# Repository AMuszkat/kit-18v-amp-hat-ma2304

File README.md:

# kit-18v-amp-hat-ma2304

A Raspberry Pi sound card with two MA2304xNS Class-D amplifiers and an MP3428 boost converter that powers the amps from a single- or dual-cell battery. For portable and mains powered applications.

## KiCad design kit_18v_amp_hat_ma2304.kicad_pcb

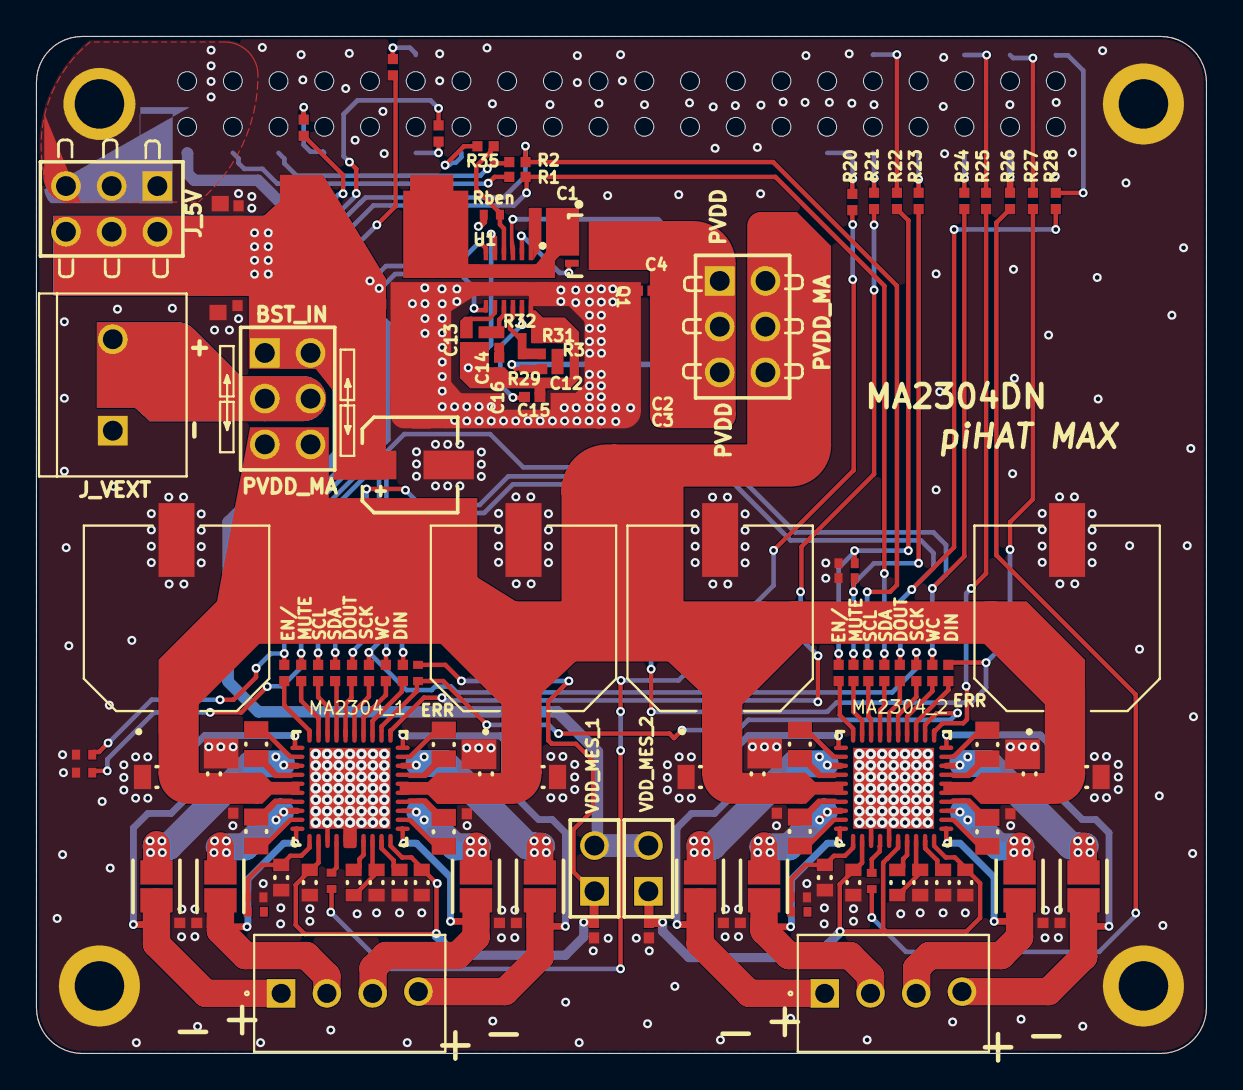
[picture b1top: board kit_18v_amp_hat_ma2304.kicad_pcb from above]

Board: 4 copper layers, 65.0 x 56.5 mm, 137 parts (1 on the bottom side), 107 nets.

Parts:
C1, C4, C10, C11, C13, C15, C16, C18, C19_1, C19_2: Cap; CAP0402_IPC_B
C2, C3, C6, C7: Cap; CAP1206_IPC_B
C5: EMZR350ARA470ME61G; PNSC-FT-V-53x53-2_V
C8, C9, C17: Cap; CAP0603_IPC_B
C12, C14: NP 0402; CAP0402_IPC_B
CADC_IN_1, CADC_IN_2: NP 0603; CAPC0603(1608)100_L
Cavdd_reg_1, Cavdd_reg_2: Cap; CAPC0603(1608)100_L
Ccd_dig_1, Ccd_dig_2: Cap; CAPC0603(1608)100_L
CflyA0_1, CflyA0_2, CflyA1_1, CflyA1_2: Cap; CAPC0805(2012)145_L
CflyB0_1, CflyB0_2, CflyB1_1, CflyB1_2: Cap; CAPC0805(2012)145_L
Cout0A_1, Cout0A_2, Cout0B_1, Cout0B_2, Cout1A_1, Cout1A_2, Cout1B_1, Cout1B_2: Cap; CAP0402_IPC_B
Cpvdd00_1, Cpvdd00_2, Cpvdd01_1, Cpvdd01_2, Cpvdd10_1, Cpvdd10_2, Cpvdd11_1, Cpvdd11_2: Cap; CAP0402_IPC_B
Cpvdd02_1, Cpvdd02_2, Cpvdd12_1, Cpvdd12_2: Cap; CAPC0603(1608)100_L
Cpvdd03_1, Cpvdd03_2, Cpvdd13_1, Cpvdd13_2: Cap; CAPC0805(2012)145_L
Cpvdd04_1, Cpvdd14_1: CAP; CAP_EEEFN1E821UL
Cpvdd04_2, Cpvdd14_2: Cap; CAP_EEEFN1E821UL
Cvdd_1, Cvdd_2: Cap; CAPC0603(1608)100_L
Cvdd_IO_1, Cvdd_IO_2: Cap; CAPC0603(1608)100_L
Cvdd_reg_1, Cvdd_reg_2: Cap; CAPC0603(1608)100_L
J_5V: 61300621121
J_PVDD: 61300621121
J_VEXT: 282837-2; TE_282837-2
J_VSEL: 61300621121
Jout1, Jout2: 282834-4; HDRV4W85P254_4X1_1062X650X1000
L1: Inductor; MPX1D0840
Lout0A_1, Lout0A_2, Lout0B_1, Lout0B_2, Lout1A_1, Lout1A_2, Lout1B_1, Lout1B_2: Ferrite; FP-NFZ2MSD-IPC_B
MA2304_1, MA2304_2: MA120_A23; QFN50P600X600X100_HS-41N
P1: Header 20X2; CLH-120-F-D-BE
Q1: IRFHM830PbF; FP-PQFN3_3x3_3-B-MFG
R1, R2, R4, R5, R6, R7, R8, R9, R10, R11, R12, R13, R14, R15, R16, R17, R18, R19, R20, R21, R22, R23, R24, R25, R26, R27, R28, R30, R33, R34, R35: 18r 0402 1%; RES0402_IPC_B
R3: NP 0402; RESC0402(1005)_L
R29, R31: Res; RESC0402(1005)_L
R32: Cap; RESC0402(1005)_L
RADC_IN1_1, RADC_IN1_2, RADC_IN2_1, RADC_IN2_2: Res; RESC0402(1005)_L
RMSEL_1, RMSEL_2: Res; RESC0402(1005)_L
Rben: Res; RESC0402(1005)_L
Ren1, Ren2: Res; RESC0402(1005)_L
Rmute1, Rmute2: Res; RESC0402(1005)_L
Rpwm_sync: Res; RESC0402(1005)_L
U1: MP3428AGL
VDD_MES_1, VDD_MES_2: 61300211121

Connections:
AMP1_ENABLE: R9.1, R16.1, Ren1.2
AMP1_ERR: MA2304_1.11, R21.1
AMP1_MSEL: R20.1, RMSEL_1.1
AMP1_MUTE: R14.1, R34.1, Rmute1.2
AMP2_ENABLE: R17.1, R22.2, Ren2.2
AMP2_ERR: MA2304_2.11, R25.2
AMP2_MSEL: R26.1, RMSEL_2.1
AMP2_MUTE: R15.1, R23.1, Rmute2.2
BST_EN: R35.1, Rben.2, U1.4
BST_IN: C5.1, C6.2, C7.2, C8.2, C9.2, C10.2, C11.2, C17.2, C18.2, J_5V.2, J_5V.4, J_5V.6, J_VSEL.1, J_VSEL.2, L1.1, U1.6, U1.11
ENABLE_1: MA2304_1.20, R16.2
ENABLE_2: MA2304_2.20, R17.2
GND: C2.1, C3.1, C4.1, C5.2, C6.1, C7.1, C8.1, C9.1, C10.1, C11.1, C17.1, C18.1, C19_1.1, C19_2.1, CADC_IN_1.2, CADC_IN_2.2, Cavdd_reg_1.2, Cavdd_reg_2.2, Cout0A_1.2, Cout0A_2.2, Cout0B_1.1, Cout0B_2.1, Cout1A_1.2, Cout1A_2.2, Cout1B_1.1, Cout1B_2.1, Cpvdd00_1.1, Cpvdd00_2.1, Cpvdd01_1.1, Cpvdd01_2.1, Cpvdd02_1.1, Cpvdd02_2.1, Cpvdd03_1.2, Cpvdd03_2.2, Cpvdd04_1.2, Cpvdd04_2.2, Cpvdd10_1.1, Cpvdd10_2.1, Cpvdd11_1.1, Cpvdd11_2.1, Cpvdd12_1.1, Cpvdd12_2.1, Cpvdd13_1.2, Cpvdd13_2.2, Cpvdd14_1.2, Cpvdd14_2.2, Cvdd_1.2, Cvdd_2.2, Cvdd_IO_1.2, Cvdd_IO_2.2, Cvdd_reg_1.2, Cvdd_reg_2.2, J_VEXT.1, MA2304_1.33, MA2304_1.35, MA2304_1.36, MA2304_1.41, MA2304_2.33, MA2304_2.35, MA2304_2.41, P1.6, P1.9, P1.14, P1.20, P1.25, P1.30, P1.34, P1.39, RADC_IN1_1.1, RADC_IN1_2.1, Rben.1, Ren1.1, Ren2.1, Rmute1.1, Rmute2.1, U1.9, U1.10, U1.17, U1.18, U1.22
I2C_SCL: R2.1, R30.1, R33.1
I2C_SCL_1: MA2304_1.18, R30.2
I2C_SCL_2: MA2304_2.18, R33.2
I2C_SDA: R1.1, R18.1, R19.1
I2C_SDA_1: MA2304_1.17, R18.2
I2C_SDA_2: MA2304_2.17, R19.2
I2S/TDM_DI_1: MA2304_1.16, R12.2
I2S/TDM_DI_2: MA2304_2.16, R13.2
I2S/TDM_DO_1: MA2304_1.13, R4.2
I2S/TDM_DO_2: MA2304_2.13, R5.2
I2S/TDM_SCK_1: MA2304_1.15, R10.2
I2S/TDM_SCK_2: MA2304_2.15, R11.2
I2S/TDM_WC_1: MA2304_1.14, R6.2
I2S/TDM_WC_2: MA2304_2.14, R8.2
I2S_DIN: R4.1, R5.1, R27.2
I2S_DOUT: R12.1, R13.1, R28.2
I2S_SCK: R7.2, R10.1, R11.1
I2S_WC: R6.1, R8.1, R24.1
MP_AGND: C13.2, C14.1, C15.1, C16.1, R31.2, U1.5, U1.16
MUTE_1: MA2304_1.19, R14.2
MUTE_2: MA2304_2.19, R15.2
NetC1_1: C1.1, L1.2, Q1.1, Q1.2, Q1.3, U1.7, U1.8, U1.19, U1.20, U1.21
NetC1_2: C1.2, U1.1
NetC12_1: C12.1, R3.1
NetC13_1: C13.1, U1.12
NetC14_2: C14.2, R32.1, U1.13
NetC15_2: C15.2, U1.15
NetC16_2: C16.2, R32.2
NetCADC_IN_1_1: CADC_IN_1.1, MA2304_1.31, RADC_IN1_1.2, RADC_IN2_1.2
NetCADC_IN_2_1: CADC_IN_2.1, MA2304_2.31, RADC_IN1_2.2, RADC_IN2_2.2
NetCavdd_reg_1_1: Cavdd_reg_1.1, MA2304_1.39
NetCavdd_reg_2_1: Cavdd_reg_2.1, MA2304_2.39
NetCcd_dig_1_1: Ccd_dig_1.1, Cvdd_reg_1.1, MA2304_1.38
NetCcd_dig_1_2: Ccd_dig_1.2, MA2304_1.37
NetCcd_dig_2_1: Ccd_dig_2.1, Cvdd_reg_2.1, MA2304_2.38
NetCcd_dig_2_2: Ccd_dig_2.2, MA2304_2.37
NetCflyA0_1_1: CflyA0_1.1, MA2304_1.2
NetCflyA0_1_2: CflyA0_1.2, MA2304_1.4
NetCflyA0_2_1: CflyA0_2.1, MA2304_2.2
NetCflyA0_2_2: CflyA0_2.2, MA2304_2.4
NetCflyA1_1_1: CflyA1_1.1, MA2304_1.27
NetCflyA1_1_2: CflyA1_1.2, MA2304_1.29
NetCflyA1_2_1: CflyA1_2.1, MA2304_2.27
NetCflyA1_2_2: CflyA1_2.2, MA2304_2.29
NetCflyB0_1_1: CflyB0_1.1, MA2304_1.7
NetCflyB0_1_2: CflyB0_1.2, MA2304_1.9
NetCflyB0_2_1: CflyB0_2.1, MA2304_2.7
NetCflyB0_2_2: CflyB0_2.2, MA2304_2.9
NetCflyB1_1_1: CflyB1_1.1, MA2304_1.24
NetCflyB1_1_2: CflyB1_1.2, MA2304_1.22
NetCflyB1_2_1: CflyB1_2.1, MA2304_2.24
NetCflyB1_2_2: CflyB1_2.2, MA2304_2.22
NetMA2304_1_34: MA2304_1.34, RMSEL_1.2
NetMA2304_2_34: MA2304_2.34, RMSEL_2.2
NetP1_3: P1.3, R1.2
NetP1_5: P1.5, R2.2
NetP1_7: P1.7, R9.2
NetP1_11: P1.11, R34.2
NetP1_12: P1.12, R7.1
NetP1_13: P1.13, R35.2
NetP1_29: P1.29, R20.2
NetP1_31: P1.31, R21.2
NetP1_32: P1.32, R22.1
NetP1_33: P1.33, R23.2
NetP1_35: P1.35, R24.2
NetP1_36: P1.36, R25.1
NetP1_37: P1.37, R26.2
NetP1_38: P1.38, R27.1
NetP1_40: P1.40, R28.1
NetQ1_4: Q1.4, U1.2
NetR3_2: R3.2, R29.2, R31.1, U1.14
OUT0A_1: Lout0A_1.2, MA2304_1.3
OUT0A_2: Lout0A_2.2, MA2304_2.3
OUT0B_1: Lout0B_1.2, MA2304_1.8
OUT0B_2: Lout0B_2.2, MA2304_2.8
OUT1A_1: Lout1A_1.1, MA2304_1.28
OUT1A_2: Lout1A_2.1, MA2304_2.28
OUT1B_1: Lout1B_1.1, MA2304_1.23
OUT1B_2: Lout1B_2.1, MA2304_2.23
PVDD: C2.2, C3.2, C4.2, C12.2, J_PVDD.1, J_PVDD.3, J_PVDD.5, Q1.5-6-7-8, R29.1, U1.3
PVDD_MA: Cpvdd00_1.2, Cpvdd00_2.2, Cpvdd01_1.2, Cpvdd01_2.2, Cpvdd02_1.2, Cpvdd02_2.2, Cpvdd03_1.1, Cpvdd03_2.1, Cpvdd04_1.1, Cpvdd04_2.1, Cpvdd10_1.2, Cpvdd10_2.2, Cpvdd11_1.2, Cpvdd11_2.2, Cpvdd12_1.2, Cpvdd12_2.2, Cpvdd13_1.1, Cpvdd13_2.1, Cpvdd14_1.1, Cpvdd14_2.1, J_PVDD.2, J_PVDD.4, J_PVDD.6, J_VSEL.5, J_VSEL.6, MA2304_1.5, MA2304_1.6, MA2304_1.25, MA2304_1.26, MA2304_2.5, MA2304_2.6, MA2304_2.25, MA2304_2.26
PWM_SYNC: MA2304_1.12, MA2304_2.12, Rpwm_sync.1
SPEAK0A_1: Cout0A_1.1, Jout1.3, Lout0A_1.1, MA2304_1.1
SPEAK0A_2: Cout0A_2.1, Jout2.3, Lout0A_2.1, MA2304_2.1
SPEAK0B_1: Cout0B_1.2, Jout1.4, Lout0B_1.1, MA2304_1.10
SPEAK0B_2: Cout0B_2.2, Jout2.4, Lout0B_2.1, MA2304_2.10
SPEAK1A_1: Cout1A_1.1, Jout1.2, Lout1A_1.2, MA2304_1.30
SPEAK1A_2: Cout1A_2.1, Jout2.2, Lout1A_2.2, MA2304_2.30
SPEAK1B_1: Cout1B_1.2, Jout1.1, Lout1B_1.2, MA2304_1.21
SPEAK1B_2: Cout1B_2.2, Jout2.1, Lout1B_2.2, MA2304_2.21
VCC_5V: J_5V.1, J_5V.3, J_5V.5, P1.2, P1.4
VDD: C19_1.2, C19_2.2, Cvdd_1.1, Cvdd_2.1, Cvdd_IO_1.1, Cvdd_IO_2.1, MA2304_1.32, MA2304_1.40, MA2304_2.32, MA2304_2.36, MA2304_2.40, Rpwm_sync.2, VDD_MES_1.1, VDD_MES_2.1
VDD_3V3: P1.1, VDD_MES_1.2, VDD_MES_2.2
VEXT: J_VEXT.2, J_VSEL.3, J_VSEL.4
